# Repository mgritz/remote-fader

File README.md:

# Remote Fader Firmware for the Datasat AP20 Digital Cinema Audio Processor

## Why is this here?

_Skip if you don't care about fluff._

Well, easy. During my days in university I joined the student cinema group.
As it happened in those days I was able to contribute to the major task of
replacing the outdated analog projection equipment in our theatre with more
up-to-date equipment. Along with a digital projector and some other equipment
we acquired a new Datasat AP20 audio processor.

Long story short, we needed a simple rotary knob _inside_ the cinema theatre for
the supervisor to control the overall volume during a film show while the actual
audio processor sits upstairs in the projector room. Buying the knob from
Datasat was not an option simply because of the hefty price tag.

But we found that Datasat implements a rather simple ASCII based protocol to
handle a whole bunch of settings on their devices and the AP20 has several
interfaces we could use with RS232 being among those. So we traced a cable
through the building...

The first approach was a TI MSP430 Launchpad with an Alps rotary encoder knob
connected that single-directionally transmits ASCII commands to the AP20. But
would't it be cool to have something with also a display?

## What is this?

The coolest type of display we could come up with for a volume control knob to
be used in a dark room is a Nixie tube display.

The PCB in this project connects two digits of IN12b Nixie tubes to an
MSP430G2553. There are two galvanically isolated voltage domains to protect the 
expensive AP20 against surges from the make-shift high voltage supply of the
Nixies.

The application code mainly does two things:
1. Whenever the knob is turned a volume command 'FADER +x\r' is transmitted
   towards the AP20 via UART. That, in turn, causes the AP20 to respond...
2. ... with a 'FADER xx\r' string denominating the current volume level.
   The number is extracted and displayed on the nixies.

Due to poor (but for now, uncorrectable) PCB design choices there must be some
additional glue and safety around the I2C connection between the MSP and the
MAX GPIO expander IC on the other side of the voltage safety barrier.

## Building and Contributing

This is not tested yet and sort of a long running project of mine.
I am using TI Code Composer Studio 8.3 and TI MSP compiler v18.1.5 on Windows
and the programmer-part of the MSP430 Launchpad for debugging.

Documentation for the AP20 and other helpful stuff: \\
http://www.film-tech.com \\
http://www.film-tech.com/warehouse/manuals/TM-H392_V1.2_AP20.pdf

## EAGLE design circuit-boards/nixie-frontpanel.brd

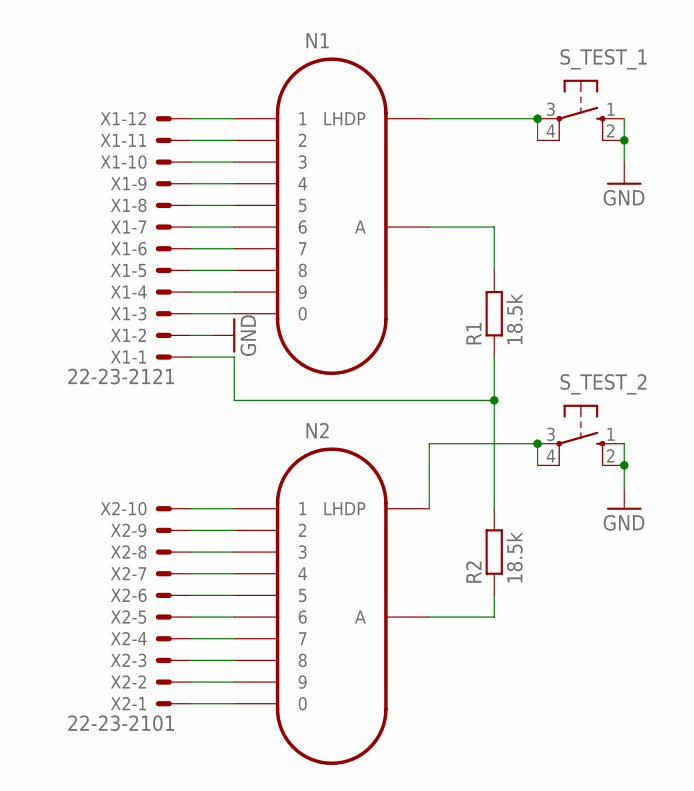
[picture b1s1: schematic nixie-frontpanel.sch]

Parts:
N1, N2: IN-12B; IN-12
R1, R2: 18.5k; M0805
S_TEST_1, S_TEST_2: 10-XX; B3F-10XX
X1: 22-23-2121
X2: 22-23-2101

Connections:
GND: S_TEST_1.1 (S), S_TEST_1.2 (S1), S_TEST_2.1 (S), S_TEST_2.2 (S1), X1.2
unnamed: N1.1, X1.12
unnamed: N1.2, X1.11
unnamed: N1.3, X1.10
unnamed: N1.4, X1.9
unnamed: N1.5, X1.8
unnamed: N1.6, X1.7
unnamed: N1.7, X1.6
unnamed: N1.8, X1.5
unnamed: N1.9, X1.4
unnamed: N1.0, X1.3
unnamed: N2.1, X2.10
unnamed: N2.2, X2.9
unnamed: N2.3, X2.8
unnamed: N2.4, X2.7
unnamed: N2.5, X2.6
unnamed: N2.6, X2.5
unnamed: N2.7, X2.4
unnamed: N2.8, X2.3
unnamed: N2.9, X2.2
unnamed: N2.0, X2.1
unnamed: R1.1, R2.2, X1.1
unnamed: N1.A, R1.2
unnamed: N2.A, R2.1
unnamed: N1.LHDP, S_TEST_1.3, S_TEST_1.4 (P1)
unnamed: N2.LHDP, S_TEST_2.3, S_TEST_2.4 (P1)

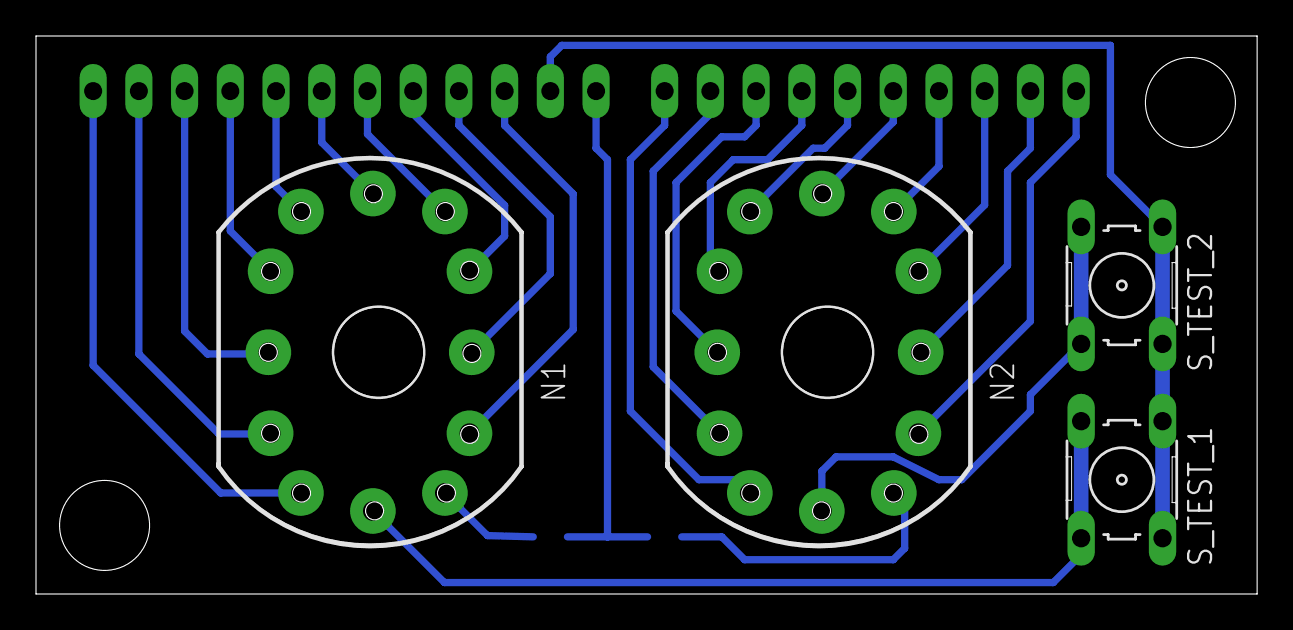
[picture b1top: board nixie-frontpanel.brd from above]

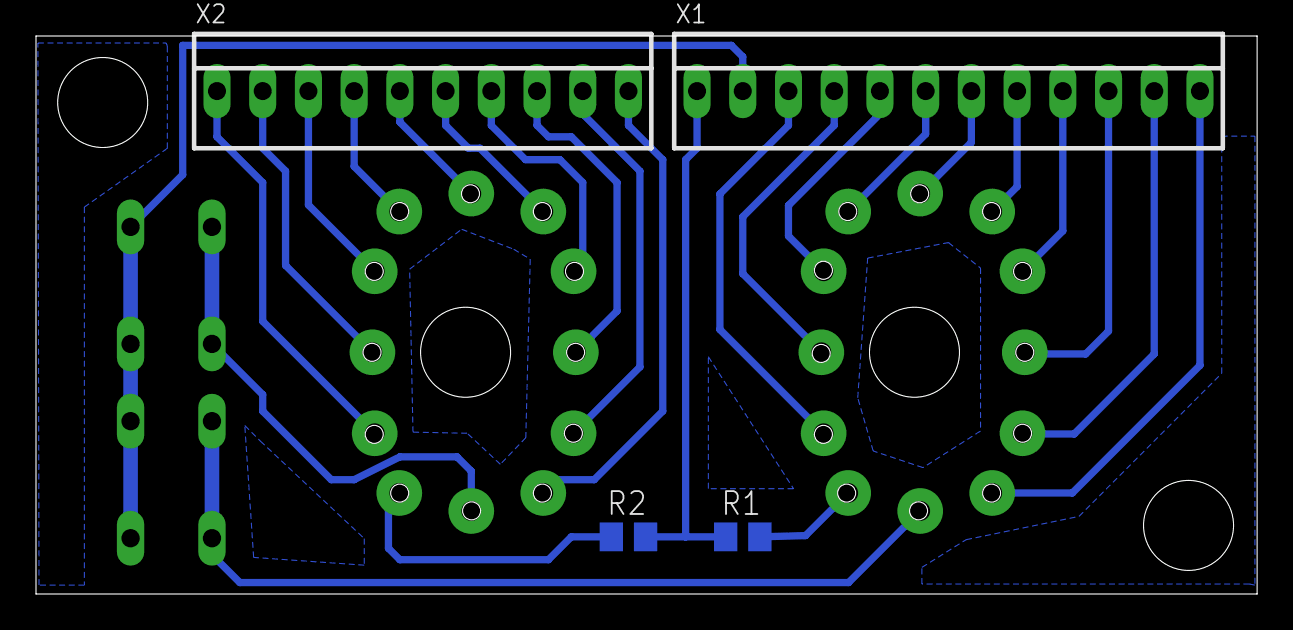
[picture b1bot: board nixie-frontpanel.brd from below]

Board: 2 copper layers, 67.8 x 31.0 mm, 8 parts (4 on the bottom side), 26 nets.

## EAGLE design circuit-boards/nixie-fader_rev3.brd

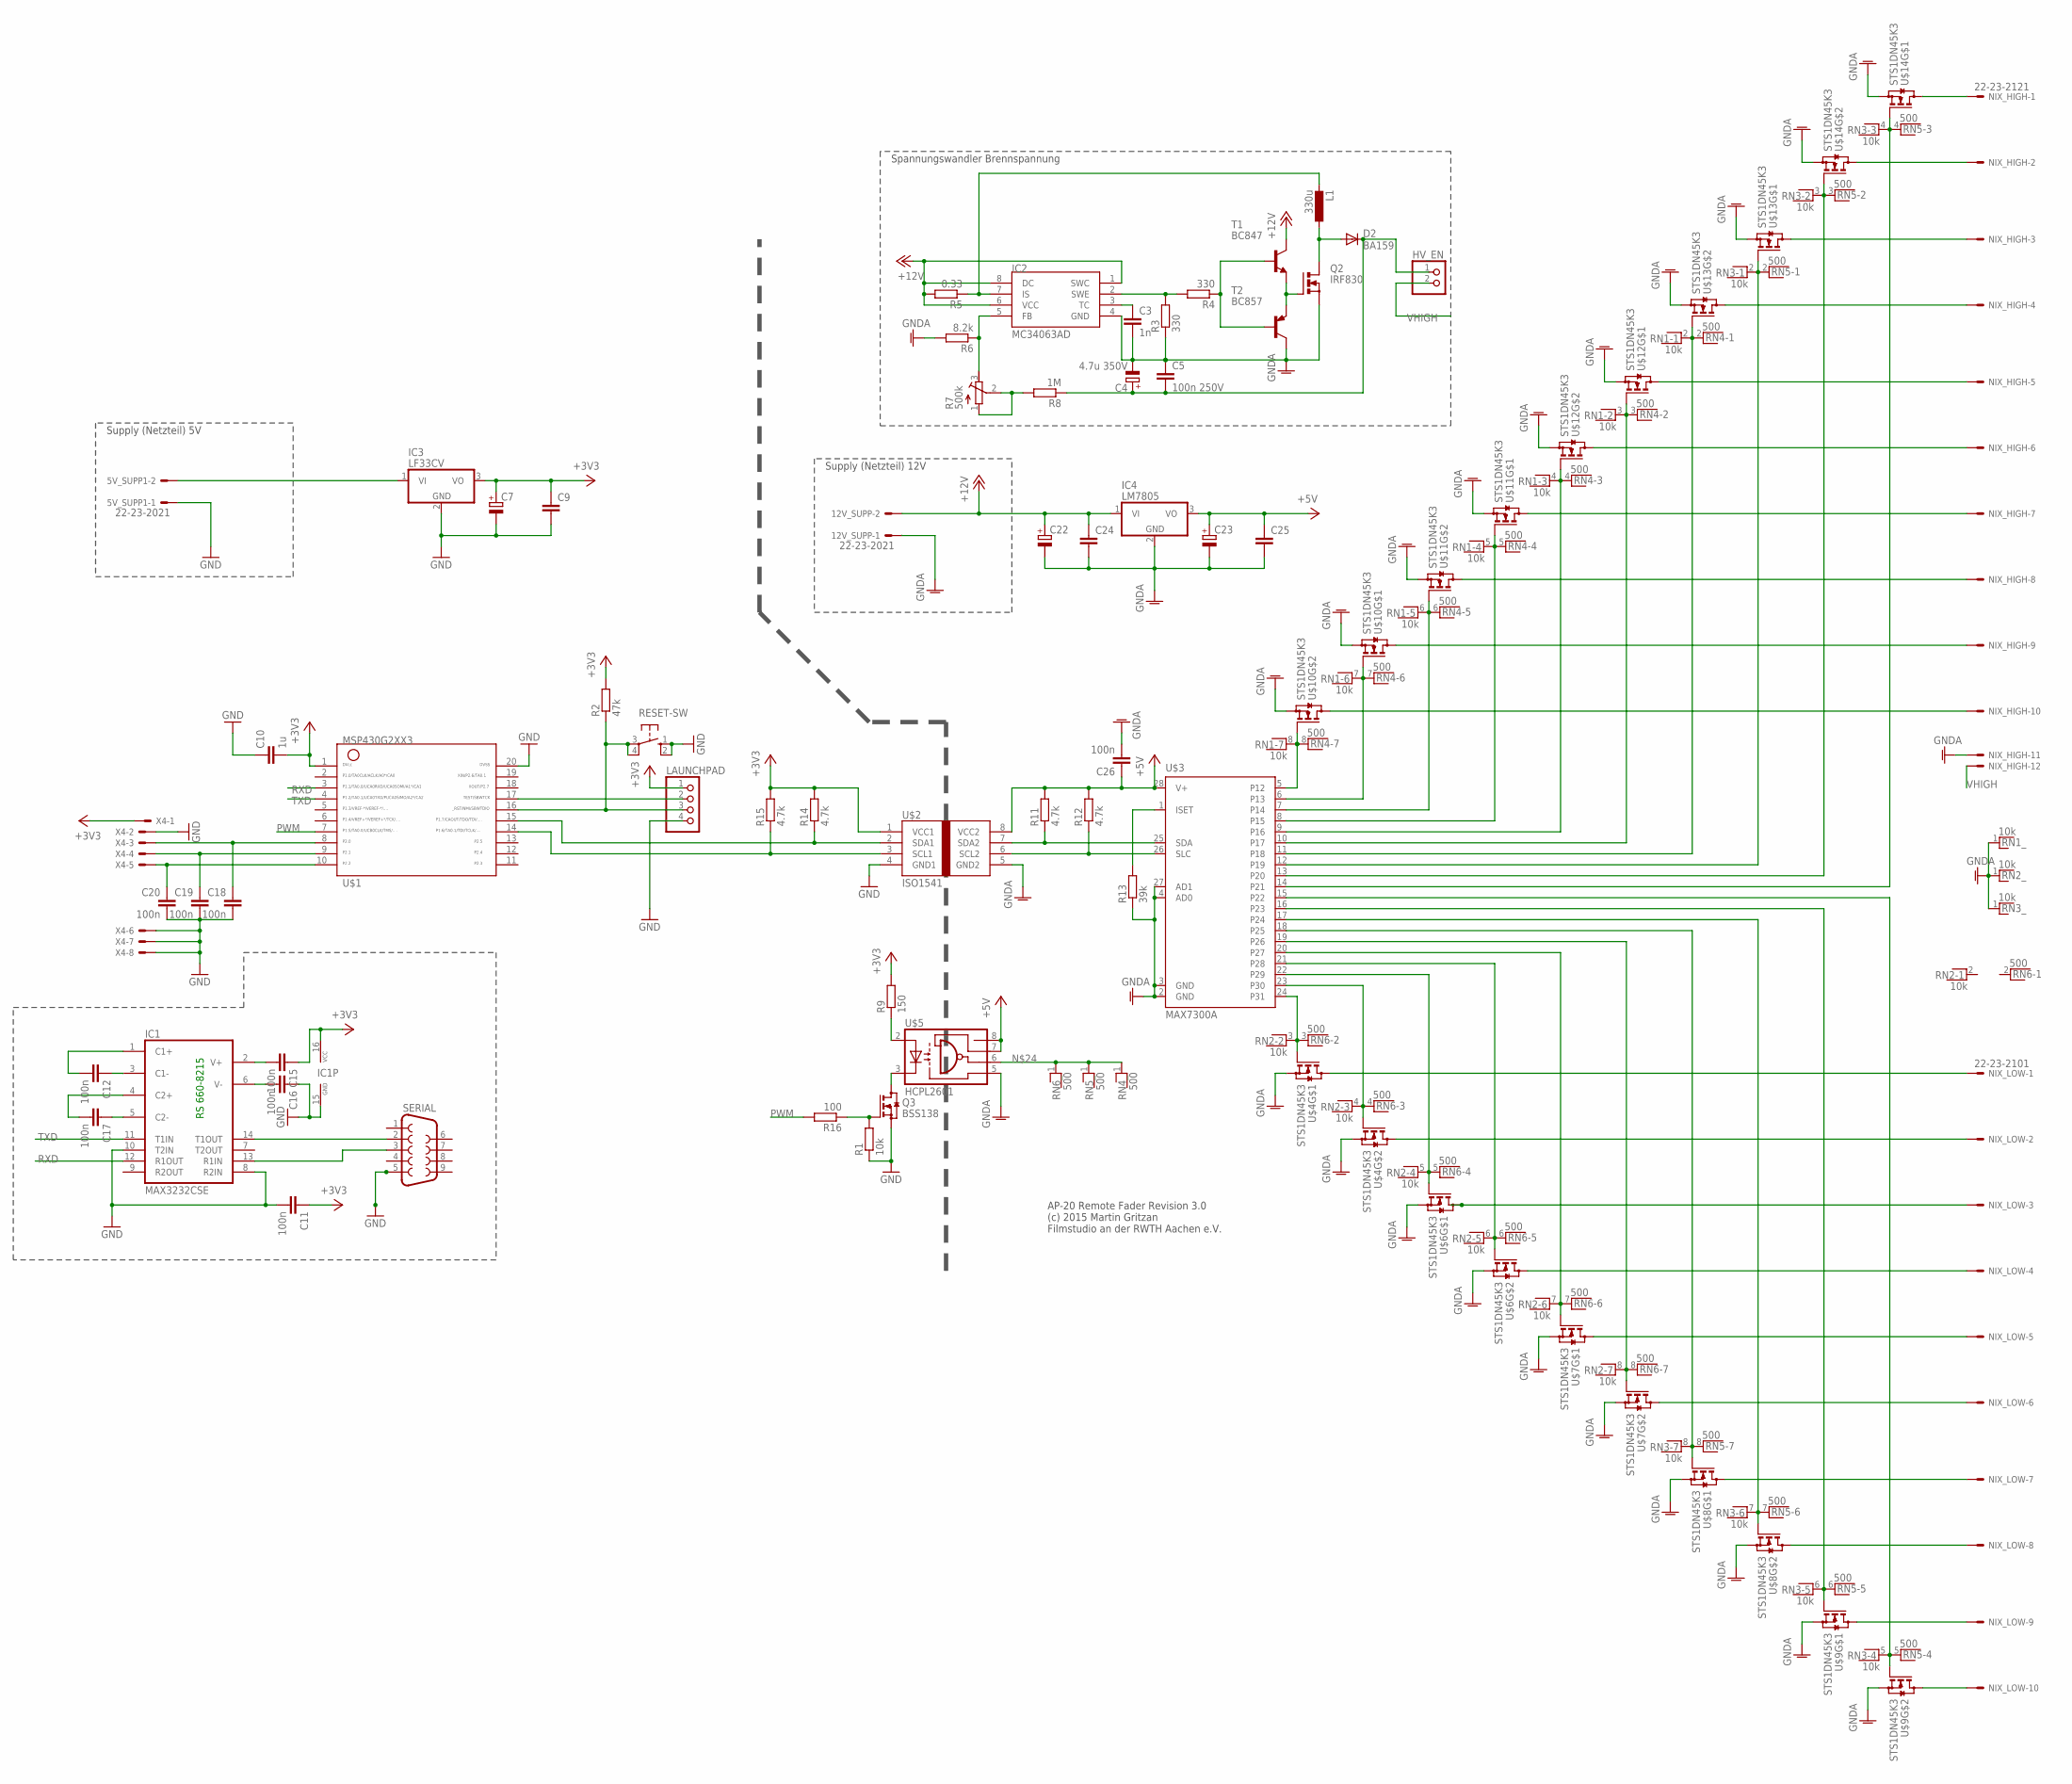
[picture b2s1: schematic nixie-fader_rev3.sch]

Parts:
5V_SUPP1, 12V_SUPP: 22-23-2021
C3: 1n; C0805
C4: 4.7u 350V; E5-8,5
C5: 100n 250V; C050-024X044
C7, C22, C23: CPOL-EU140CLH-0810; 140CLH-0810
C9, C24, C25: C-EUC0805K; C0805K
C10: 1u; C0805K
C11, C12, C15, C16, C17, C18, C19, C20, C26: 100n; C0805
D2: BA159; P1-10
HV_EN: PINHD-1X2; 1X02
IC1: MAX3232CSE; SO16
IC2: MC34063AD; SOIC8
IC3: LF33CV; TO220V
IC4: LM7805; TO220V
L1: 330u; IRF36
LAUNCHPAD: PINHD-1X4; 1X04
NIX_HIGH: 22-23-2121
NIX_LOW: 22-23-2101
Q2: IRF830; TO220BV
Q3: BSS138; SOT23
R1: 10k; M0805
R2: 47k; R0805
R3, R4: 330; M0805
R5: 0.33; M0805
R6: 8.2k; M0805
R7: 500k; RTRIM3296Y
R8: 1M; M0805
R9: 150; M0805
R11, R12, R14, R15: 4.7k; M0805
R13: 39k; M0805
R16: 100; M0805
RESET-SW: 10-XX; B3F-10XX
RN1, RN2, RN3: 10k; RN-8
RN4, RN5, RN6: 500; RN-8
SERIAL: F09H
T1: BC847; SOT23
T2: BC857; SOT23-BEC
U$1: G2XX3---PW20; PW20
U$2: ISO1541; SOIC8
U$3: MAX7300A; SSOP28
U$4, U$6, U$7, U$8, U$9, U$10, U$11, U$12, U$13, U$14: STS1DN45K3; SO08
U$5: HCPL2601; DIP8-SMD
X4: 22-23-2081

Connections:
+3V3: C7.+, C9.1, C10.2, C11.1, C15.1, IC1.16 (VCC), IC3.3 (VO), LAUNCHPAD.1, R2.2, R9.2, R14.2, R15.2, U$1.1, U$2.1 (VCC1), X4.1
+5V: C23.+, C25.1, C26.1, IC4.3 (VO), R11.2, R12.2, U$2.8 (VCC2), U$3.28 (V+), U$5.7 (EN), U$5.8 (VCC)
+12V: 12V_SUPP.2, C22.+, C24.1, IC2.1 (SWC), IC2.6 (VCC), IC2.8 (DC), IC4.1 (VI), R5.2, T1.3 (C)
GND: 5V_SUPP1.1, C7.-, C9.2, C10.1, C11.2, C16.1, C18.2, C19.2, C20.2, IC1.8 (R2IN), IC1.10 (T2IN), IC1.15 (GND), IC3.2 (GND), LAUNCHPAD.4, Q3.2 (S), R1.1, RESET-SW.1 (S), RESET-SW.2 (S1), SERIAL.5, U$1.20, U$2.4 (GND1), X4.2, X4.6, X4.7, X4.8
GNDA: 12V_SUPP.1, C3.2, C4.-, C5.1, C22.-, C23.-, C24.2, C25.2, C26.2, IC2.4 (GND), IC4.2 (GND), NIX_HIGH.11, Q2.S, R3.1, R6.2, R13.1, RN1.1, RN2.1, RN3.1, T2.C, U$2.5 (GND2), U$3.2 (GND), U$3.3 (GND), U$3.4 (AD0), U$3.27 (AD1), U$4.1 (S), U$4.3 (S), U$5.5 (GND), U$6.1 (S), U$6.3 (S), U$7.1 (S), U$7.3 (S), U$8.1 (S), U$8.3 (S), U$9.1 (S), U$9.3 (S), U$10.1 (S), U$10.3 (S), U$11.1 (S), U$11.3 (S), U$12.1 (S), U$12.3 (S), U$13.1 (S), U$13.3 (S), U$14.1 (S), U$14.3 (S)
unnamed: Q3.1 (G), R1.2, R16.1
unnamed: C12.1, IC1.3 (C1-)
unnamed: C3.1, IC2.3 (TC)
unnamed: IC2.2 (SWE), R3.2, R4.2
unnamed: R4.1, T1.1 (B), T2.B
unnamed: C17.1, IC1.5 (C2-)
unnamed: C17.2, IC1.4 (C2+)
unnamed: C16.2, IC1.6 (V-)
unnamed: C15.2, IC1.2 (V+)
unnamed: LAUNCHPAD.3, R2.1, RESET-SW.3, RESET-SW.4 (P1), U$1.16
unnamed: C12.2, IC1.1 (C1+)
unnamed: R11.1, U$2.7 (SDA2), U$3.25 (SDA)
unnamed: IC1.14 (T1OUT), SERIAL.2
unnamed: R12.1, U$2.6 (SCL2), U$3.26 (SLC)
unnamed: Q2.G, T1.2 (E), T2.E
unnamed: D2.A, L1.1, Q2.D
unnamed: IC2.7 (IS), L1.2, R5.1
unnamed: IC2.5 (FB), R6.1, R7.3 (A)
unnamed: R7.1 (E), R7.2 (S), R8.2
unnamed: C18.1, U$1.8, X4.3
unnamed: RN4.1, RN5.1, RN6.1, U$5.6 (OUT)
unnamed: C19.1, U$1.9, X4.4
unnamed: NIX_HIGH.2, U$14.5 (D), U$14.6 (D)
unnamed: C20.1, U$1.10, X4.5
unnamed: Q3.3 (D), U$5.3 (C)
unnamed: R9.1, U$5.2 (A)
unnamed: RN2.3, RN6.3, U$3.24 (P31), U$4.2 (G)
unnamed: RN1.8, RN4.8, U$3.5 (P12), U$10.4 (G)
unnamed: RN2.4, RN6.4, U$3.23 (P30), U$4.4 (G)
unnamed: RN1.7, RN4.7, U$3.6 (P13), U$10.2 (G)
unnamed: LAUNCHPAD.2, U$1.17
unnamed: RN2.5, RN6.5, U$3.22 (P29), U$6.2 (G)
unnamed: RN2.6, RN6.6, U$3.21 (P28), U$6.4 (G)
unnamed: IC1.13 (R1IN), SERIAL.3
unnamed: R13.2, U$3.1 (ISET)
unnamed: RN1.6, RN4.6, U$3.7 (P14), U$11.4 (G)
unnamed: RN2.7, RN6.7, U$3.20 (P27), U$7.2 (G)
unnamed: RN2.8, RN6.8, U$3.19 (P26), U$7.4 (G)
unnamed: RN1.5, RN4.5, U$3.8 (P15), U$11.2 (G)
unnamed: RN3.8, RN5.8, U$3.18 (P25), U$8.2 (G)
unnamed: RN3.7, RN5.7, U$3.17 (P24), U$8.4 (G)
unnamed: RN1.4, RN4.4, U$3.9 (P16), U$12.4 (G)
unnamed: RN3.6, RN5.6, U$3.16 (P23), U$9.2 (G)
unnamed: RN3.5, RN5.5, U$3.15 (P22), U$9.4 (G)
unnamed: NIX_HIGH.1, U$14.7 (D), U$14.8 (D)
unnamed: NIX_LOW.1, U$4.7 (D), U$4.8 (D)
unnamed: NIX_LOW.2, U$4.5 (D), U$4.6 (D)
unnamed: R14.1, U$1.15, U$2.2 (SDA1)
unnamed: NIX_LOW.3, U$6.7 (D), U$6.8 (D)
unnamed: NIX_LOW.4, U$6.5 (D), U$6.6 (D)
unnamed: NIX_LOW.5, U$7.7 (D), U$7.8 (D)
unnamed: NIX_LOW.6, U$7.5 (D), U$7.6 (D)
unnamed: NIX_LOW.7, U$8.7 (D), U$8.8 (D)
unnamed: NIX_LOW.8, U$8.5 (D), U$8.6 (D)
unnamed: NIX_LOW.9, U$9.7 (D), U$9.8 (D)
unnamed: R15.1, U$1.14, U$2.3 (SCL1)
unnamed: NIX_LOW.10, U$9.5 (D), U$9.6 (D)
unnamed: RN1.3, RN4.3, U$3.10 (P17), U$12.2 (G)
unnamed: RN1.2, RN4.2, U$3.11 (P18), U$13.4 (G)
unnamed: RN3.2, RN5.2, U$3.12 (P19), U$13.2 (G)
unnamed: RN3.3, RN5.3, U$3.13 (P20), U$14.4 (G)
unnamed: 5V_SUPP1.2, IC3.1 (VI)
unnamed: RN3.4, RN5.4, U$3.14 (P21), U$14.2 (G)
unnamed: NIX_HIGH.3, U$13.7 (D), U$13.8 (D)
unnamed: NIX_HIGH.4, U$13.5 (D), U$13.6 (D)
unnamed: NIX_HIGH.5, U$12.7 (D), U$12.8 (D)
unnamed: NIX_HIGH.6, U$12.5 (D), U$12.6 (D)
unnamed: NIX_HIGH.7, U$11.7 (D), U$11.8 (D)
unnamed: NIX_HIGH.8, U$11.5 (D), U$11.6 (D)
unnamed: NIX_HIGH.9, U$10.7 (D), U$10.8 (D)
unnamed: NIX_HIGH.10, U$10.5 (D), U$10.6 (D)
PWM: R16.2, U$1.7
RXD: IC1.12 (R1OUT), U$1.3
TXD: IC1.11 (T1IN), U$1.4
VHIGH: HV_EN.2, NIX_HIGH.12
VHIGH_SUP: C4.+, C5.2, D2.C, HV_EN.1, R8.1

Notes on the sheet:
Supply (Netzteil) 12V
Spannungswandler Brennspannung
RS 660-8215
AP-20 Remote Fader Revision 3.0 (c) 2015 Martin Gritzan Filmstudio an der RWTH Aachen e.V.
Supply (Netzteil) 5V

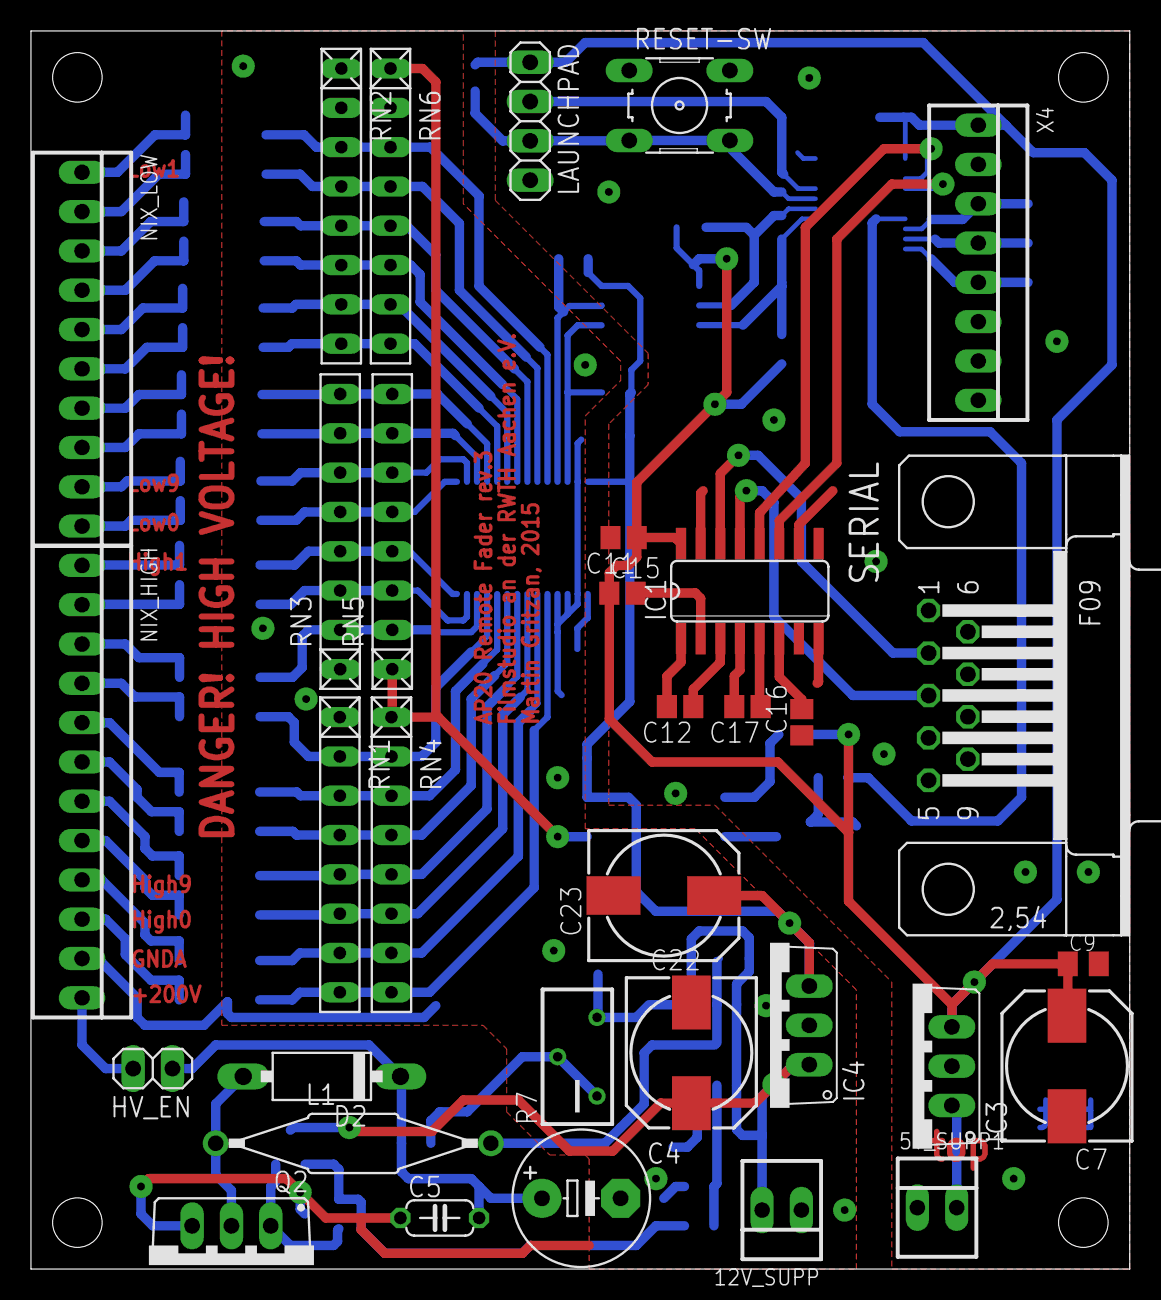
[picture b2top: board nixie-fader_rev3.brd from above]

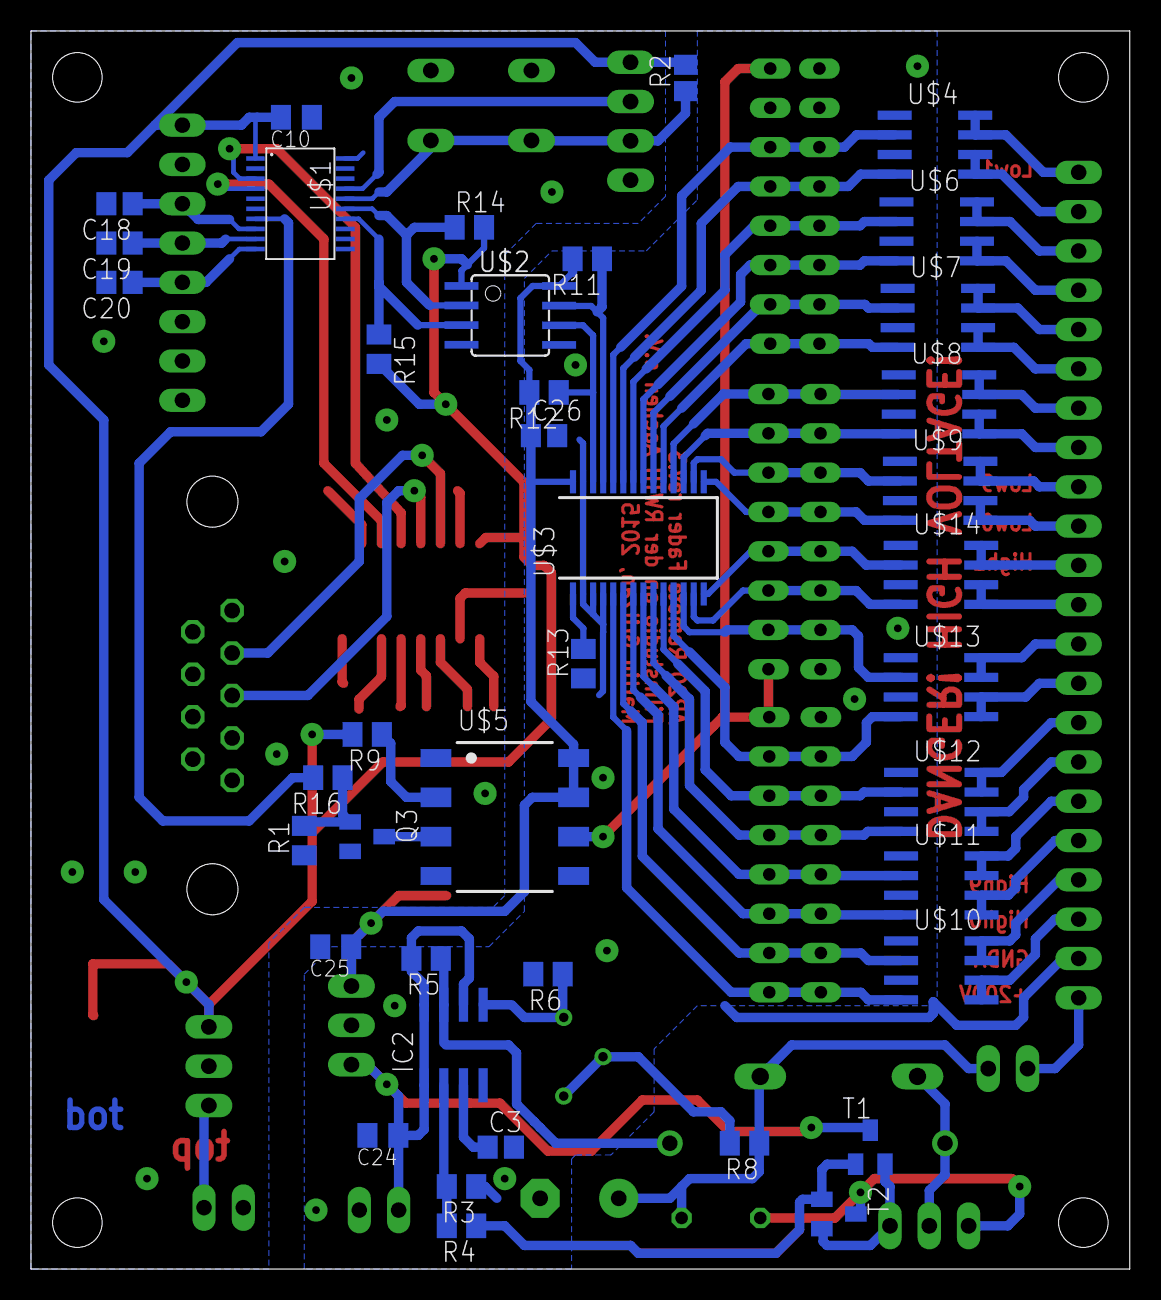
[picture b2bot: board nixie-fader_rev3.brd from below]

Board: 2 copper layers, 71.0 x 80.0 mm, 73 parts (40 on the bottom side), 81 nets.

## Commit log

2019-03-02 Initial Commit
    There already is a lot of stuff here because of ongoing development.
    Problems are marked in the files and will be fixed down the line.
2019-03-02 PCBs added
    Those are the EAGLE files. Made with EAGLE 7 or so, too long ago
    for me to remember exactly.
2019-03-02 add picture of knob connection
    This is the way the ALPS knob is meant to be connected to the PCB input.
2019-03-16 moved ALPS knob functionality into separate files
    Added some thread safety around getting the knob increments
    instead of having this directly transmit the UART.
    Also moove sys clock init to main.c - makes more sense there.
2019-03-16 move nixie stuff into own file
    re-enable uart and hopefully fix race condition in level handling.
2019-03-16 add FT's microframework as submodule
    We are interested in the ringbuffer implementation here.
2019-03-31 change uartbuf to use UFW ring-buffer
    changed C dialect to -C99 and set NDEBUG to make it
    compile without the 'assert' (that wouldn't fit into
    memory).
    Removed the state machine for parsing the input.
    That is to be done in a different module.
2019-03-31 move parsing of incoming bytes to ap20 module
2019-11-24 move i2c out of header
2020-02-08 add helpers for setting and clearing bits and GPIOs
    Those look quite cryptic otherweise...
2020-02-08 use SDA-aware I2C recovery protocol
    As suggested in this AN
    https://www.analog.com/media/en/technical-documentation/application-notes/54305147357414AN686_0.pdf
    The I2C recovery should check the SDA's state to quit recovering the slave
    as early as possible and to ensure proper STOP condition has been sent.
2020-02-08 knob uses port-helpers
2020-02-08 use Timer to safeguard I2C transaction
    The application must stay responsive even if the I2C
    got stuck due to slave not being powered.
    So we safeguard this with a timer interrupt.
2020-02-08 knob: revert away from IRQ-based debounce
    That TimerA0 stuff wasn't working anyway so, lets get rid of it.
    We can wait with a short busy loop instead.
    Cannot test it, though.
2020-02-08 nixie: re-init before each write
    Re-initialize I2C and the external GPIO expander
    because we have no way of knowing whether the 12V
    rail may have been power-cycled since the last
    write cycle.
2020-02-08 uart: allow sending const buffers
2020-02-08 nixie: switch digit outputs
    ... for more convenient mounting.
2020-02-08 debug: disable P2OUT-debugging everywhere
    Preparing to use those for Alps-knob again.
2020-02-08 knob: cleanup and re-enable
    Clean up this file a bit. Remove superflous
    method, switch to underscore naming
    everywhere and remove residue of the old
    timer-driven de-bounce.
    Reconnect increments from the knob to sending
    data to the AP20 interface's empty transmit
2020-02-08 itoa method
    Sort of a standard procedure yet missing in the stdlib I have.
    So, heaviely modified to fit my needs here.
2020-02-08 ap20: transmit fader increments
2020-02-08 add README
2020-02-12 add AP20 simulator tool
    because we need something to test the remote fader firmware against
    since we cannot test against the actual hardware
